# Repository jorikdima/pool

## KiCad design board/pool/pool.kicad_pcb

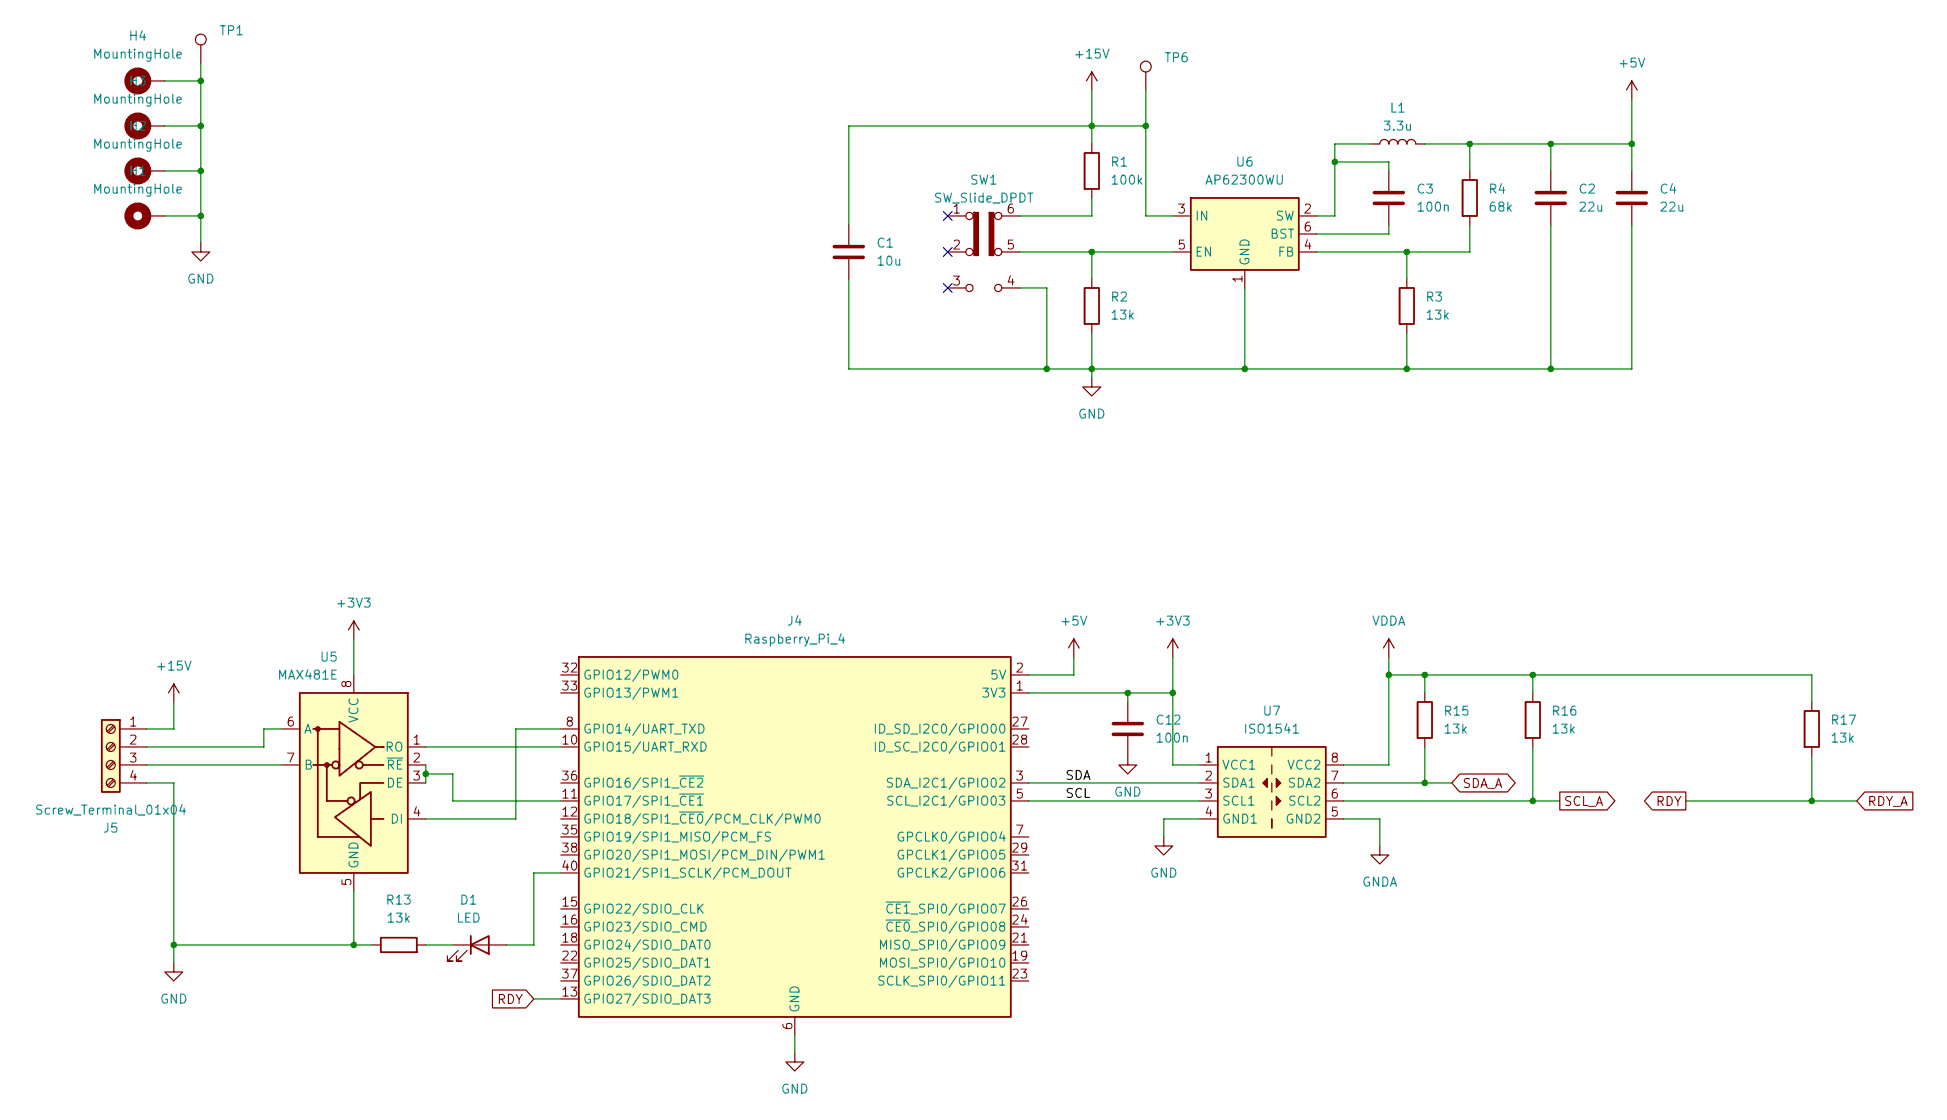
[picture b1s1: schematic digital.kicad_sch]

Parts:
C1: 10u; C_0805_2012Metric_Pad1.18x1.45mm_HandSolder
C2, C4: 22u; C_0805_2012Metric_Pad1.18x1.45mm_HandSolder
C3, C12: 100n; C_0805_2012Metric_Pad1.18x1.45mm_HandSolder
D1: LED; LED_D1.8mm_W3.3mm_H2.4mm
H1, H2, H3, H4: MountingHole; MountingHole_2.5mm_Pad_TopBottom
J4: Raspberry_Pi_4; PinSocket_2x20_P2.54mm_Vertical
J5: Screw_Terminal_01x04; TerminalBlock_Phoenix_MKDS-1,5-4_1x04_P5.00mm_Horizontal
L1: 3.3u; L_Taiyo-Yuden_NR-80xx_HandSoldering
R1: 100k; R_0805_2012Metric_Pad1.20x1.40mm_HandSolder
R2, R3, R13, R15, R16, R17: 13k; R_0805_2012Metric_Pad1.20x1.40mm_HandSolder
R4: 68k; R_0805_2012Metric_Pad1.20x1.40mm_HandSolder
SW1: SW_Slide_DPDT; CL-SB-22A
TP1: TestPoint; TestPoint_Pad_2.0x2.0mm
TP6: TestPoint; TestPoint_THTPad_1.5x1.5mm_Drill0.7mm
U5: MAX481E; SOIC-8_3.9x4.9mm_P1.27mm
U6: AP62300WU; TSOT-23-6
U7: ISO1541; SOIC-8_3.9x4.9mm_P1.27mm

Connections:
+3V3: C12.1, J4.1 (3V3), J4.17 (3V3), U5.8 (VCC), U7.1 (VCC1)
+5V: C2.1, C4.1, J4.2 (5V), J4.4 (5V), L1.2, R4.1; also elsewhere on the board
+15V: C1.1, J5.1, R1.1, TP6.1, U6.3 (IN)
/digital/SCL: J4.5 (SCL_I2C1/GPIO03), U7.3 (SCL1)
/digital/SDA: J4.3 (SDA_I2C1/GPIO02), U7.2 (SDA1)
GND: C1.2, C2.2, C4.2, C12.2, H1.1, H2.1, H3.1, H4.1, J4.6 (GND), J4.9 (GND), J4.14 (GND), J4.20 (GND), J4.25 (GND), J4.30 (GND), J4.34 (GND), J4.39 (GND), J5.4, R2.2, R3.2, R13.1, SW1.4 (A), TP1.1, U5.5 (GND), U6.1 (GND), U7.4 (GND1); also elsewhere on the board
GNDA: U7.5 (GND2); also elsewhere on the board
unnamed: D1.2 (A), J4.40 (GPIO21/SPI1_SCLK/PCM_DOUT)
unnamed: D1.1 (K), R13.2
unnamed: J4.8 (GPIO14/UART_TXD), U5.4 (DI)
unnamed: J4.10 (GPIO15/UART_RXD), U5.1 (RO)
unnamed: J4.11 (GPIO17/SPI1_~CE1), U5.2 (~RE), U5.3 (DE)
unnamed: J5.2, U5.6 (A)
unnamed: J5.3, U5.7 (B)
unnamed: R1.2, SW1.6 (C)
unnamed: C3.1, U6.6 (BST)
unnamed: R2.1, SW1.5 (B), U6.5 (EN)
unnamed: R3.1, R4.2, U6.4 (FB)
unnamed: C3.2, L1.1, U6.2 (SW)
RDY: J4.13 (GPIO27/SDIO_DAT3), R17.2; also elsewhere on the board
SCL_A: R16.2, U7.6 (SCL2); also elsewhere on the board
SDA_A: R15.2, U7.7 (SDA2); also elsewhere on the board
VDDA: R15.1, R16.1, R17.1, U7.8 (VCC2); also elsewhere on the board

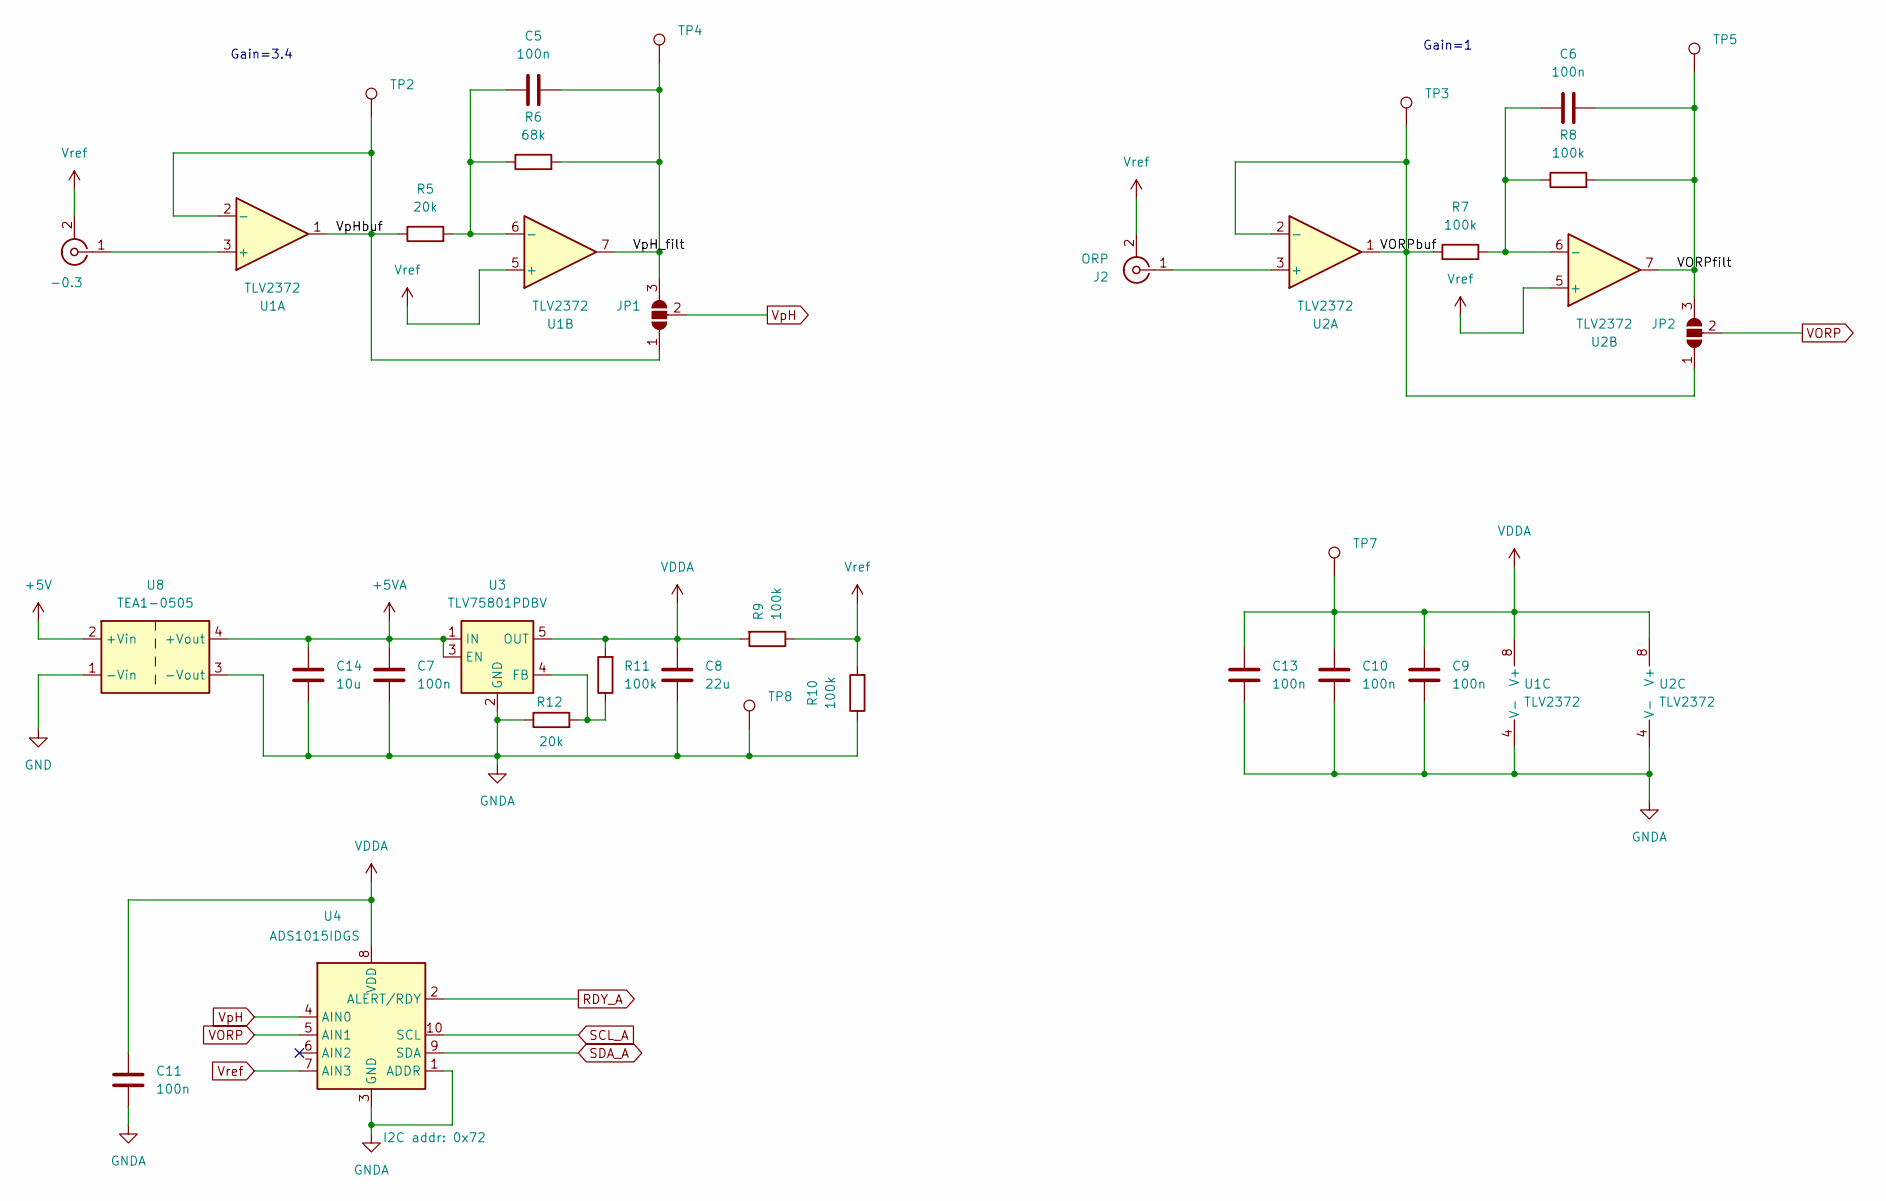
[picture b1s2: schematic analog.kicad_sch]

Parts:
C5, C6, C7, C9, C10, C11, C13: 100n; C_0805_2012Metric_Pad1.18x1.45mm_HandSolder
C8: 22u; C_0805_2012Metric_Pad1.18x1.45mm_HandSolder
C14: 10u; C_0805_2012Metric_Pad1.18x1.45mm_HandSolder
J1: -0.3; SMA_Amphenol_132134-11_Vertical
J2: ORP; SMA_Amphenol_132134-11_Vertical
JP1, JP2: SolderJumper_3_Open; SolderJumper-3_P1.3mm_Open_Pad1.0x1.5mm_NumberLabels
R5, R12: 20k; R_0805_2012Metric_Pad1.20x1.40mm_HandSolder
R6: 68k; R_0805_2012Metric_Pad1.20x1.40mm_HandSolder
R7, R8, R9, R10, R11: 100k; R_0805_2012Metric_Pad1.20x1.40mm_HandSolder
TP2, TP3, TP4, TP5: TestPoint; TestPoint_THTPad_1.5x1.5mm_Drill0.7mm
TP7: GNDA; TestPoint_THTPad_1.5x1.5mm_Drill0.7mm
TP8: GNDA; TestPoint_Pad_2.0x2.0mm
U1, U2: TLV2372; SOIC-8_3.9x4.9mm_P1.27mm
U3: TLV75801PDBV; SOT-23-5
U4: ADS1015IDGS; TSSOP-10_3x3mm_P0.5mm
U8: TEA1-0505; Converter_DCDC_TRACO_TEA1-xxxx_THT

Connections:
+5V: U8.2 (+Vin); also elsewhere on the board
+5VA: C7.1, C14.1, U3.1 (IN), U3.3 (EN), U8.4 (+Vout)
/analog/VORPbuf: JP2.1 (A), R7.1, TP3.1, U2.1, U2.2 (-)
/analog/VORPfilt: C6.1, JP2.3 (B), R8.2, TP5.1, U2.7
/analog/VpH_filt: C5.1, JP1.3 (B), R6.2, TP4.1, U1.7
/analog/VpHbuf: JP1.1 (A), R5.1, TP2.1, U1.1, U1.2 (-)
GND: U8.1 (-Vin); also elsewhere on the board
GNDA: C7.2, C8.1, C9.2, C10.2, C11.2, C13.2, C14.2, R10.1, R12.1, TP8.1, U1.4 (V-), U2.4 (V-), U3.2 (GND), U4.1 (ADDR), U4.3 (GND), U8.3 (-Vout); also elsewhere on the board
unnamed: J1.1 (In), U1.3 (+)
unnamed: J2.1 (In), U2.3 (+)
unnamed: C5.2, R5.2, R6.1, U1.6 (-)
unnamed: C6.2, R7.2, R8.1, U2.6 (-)
unnamed: R11.1, R12.2, U3.4 (FB)
RDY: U4.2 (ALERT/RDY); also elsewhere on the board
SCL_A: U4.10 (SCL); also elsewhere on the board
SDA_A: U4.9 (SDA); also elsewhere on the board
VDDA: C8.2, C9.1, C10.1, C11.1, C13.1, R9.2, R11.2, TP7.1, U1.8 (V+), U2.8 (V+), U3.5 (OUT), U4.8 (VDD); also elsewhere on the board
VORP: JP2.2 (C), U4.5 (AIN1)
VpH: JP1.2 (C), U4.4 (AIN0)
Vref: J1.2 (Ext), J2.2 (Ext), R9.1, R10.2, U1.5 (+), U2.5 (+), U4.7 (AIN3)

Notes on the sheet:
Gain=1
Gain=3.4

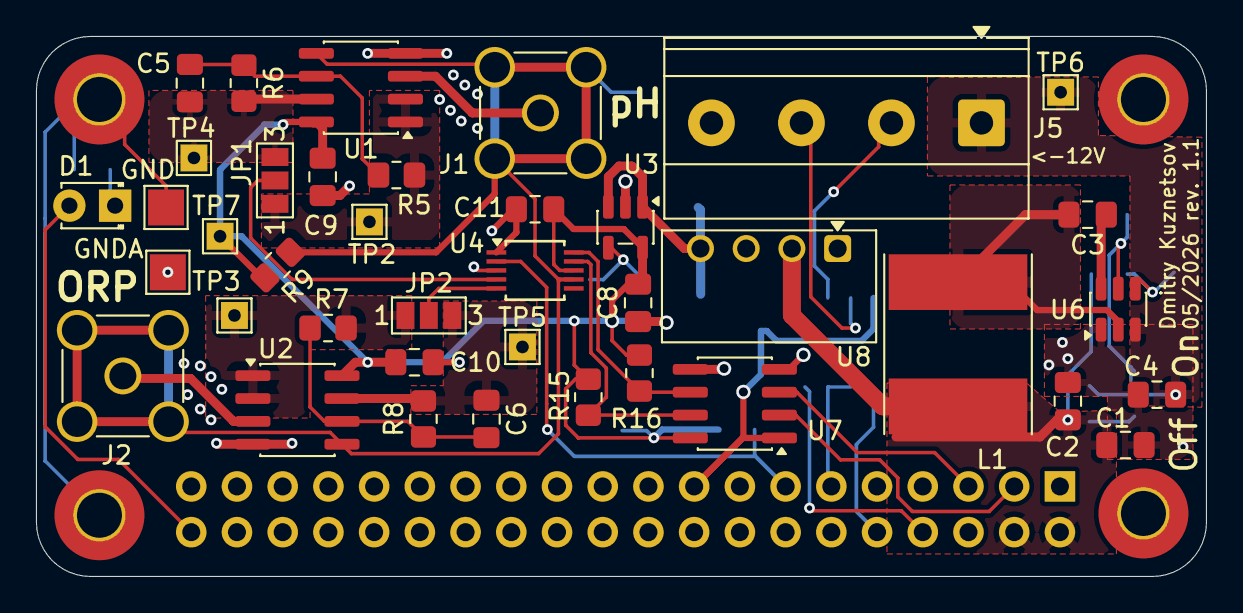
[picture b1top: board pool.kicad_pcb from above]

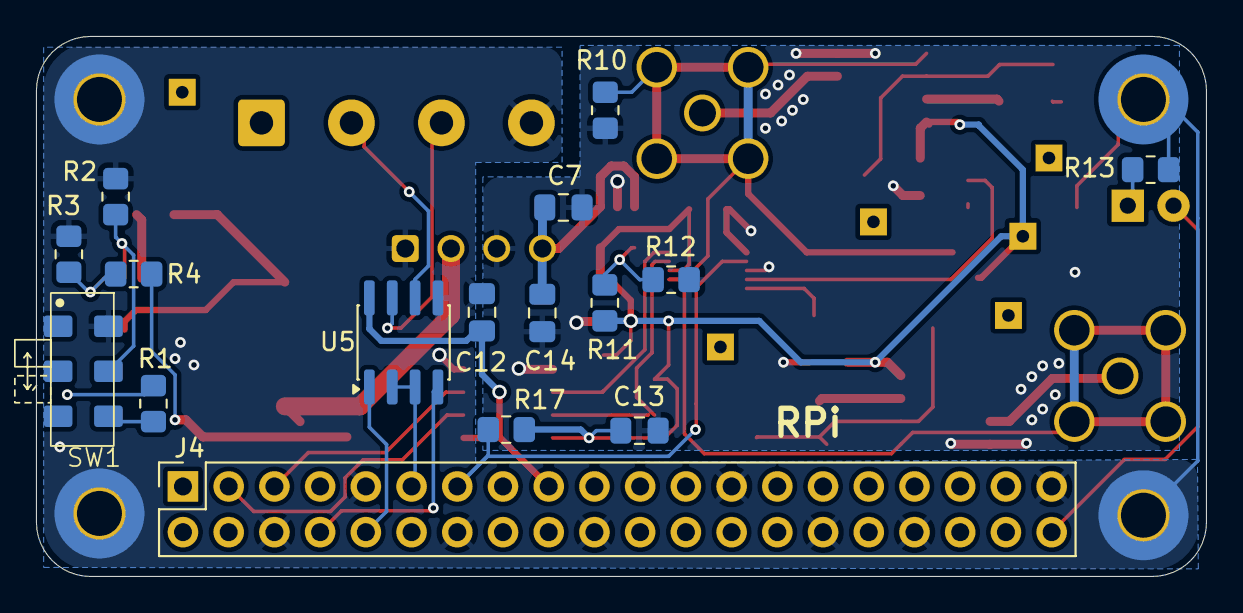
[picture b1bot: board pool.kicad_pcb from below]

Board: 2 copper layers, 65.0 x 30.0 mm, 59 parts (16 on the bottom side), 36 nets.

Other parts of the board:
GND: TestPoint; TestPoint_Pad_2.0x2.0mm
GNDA: GNDA; TestPoint_Pad_2.0x2.0mm

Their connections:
GND: GND.1; also elsewhere on the board
GNDA: GNDA.1; also elsewhere on the board

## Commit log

2026-04-26 Added rev 1.1 of the board
2026-05-02 Initial release of the case design. No latches so far
2026-05-02 Add a datasheet for the power converter
2026-05-02 Initial primitive python code
2026-05-03 Final version of the enclosure
